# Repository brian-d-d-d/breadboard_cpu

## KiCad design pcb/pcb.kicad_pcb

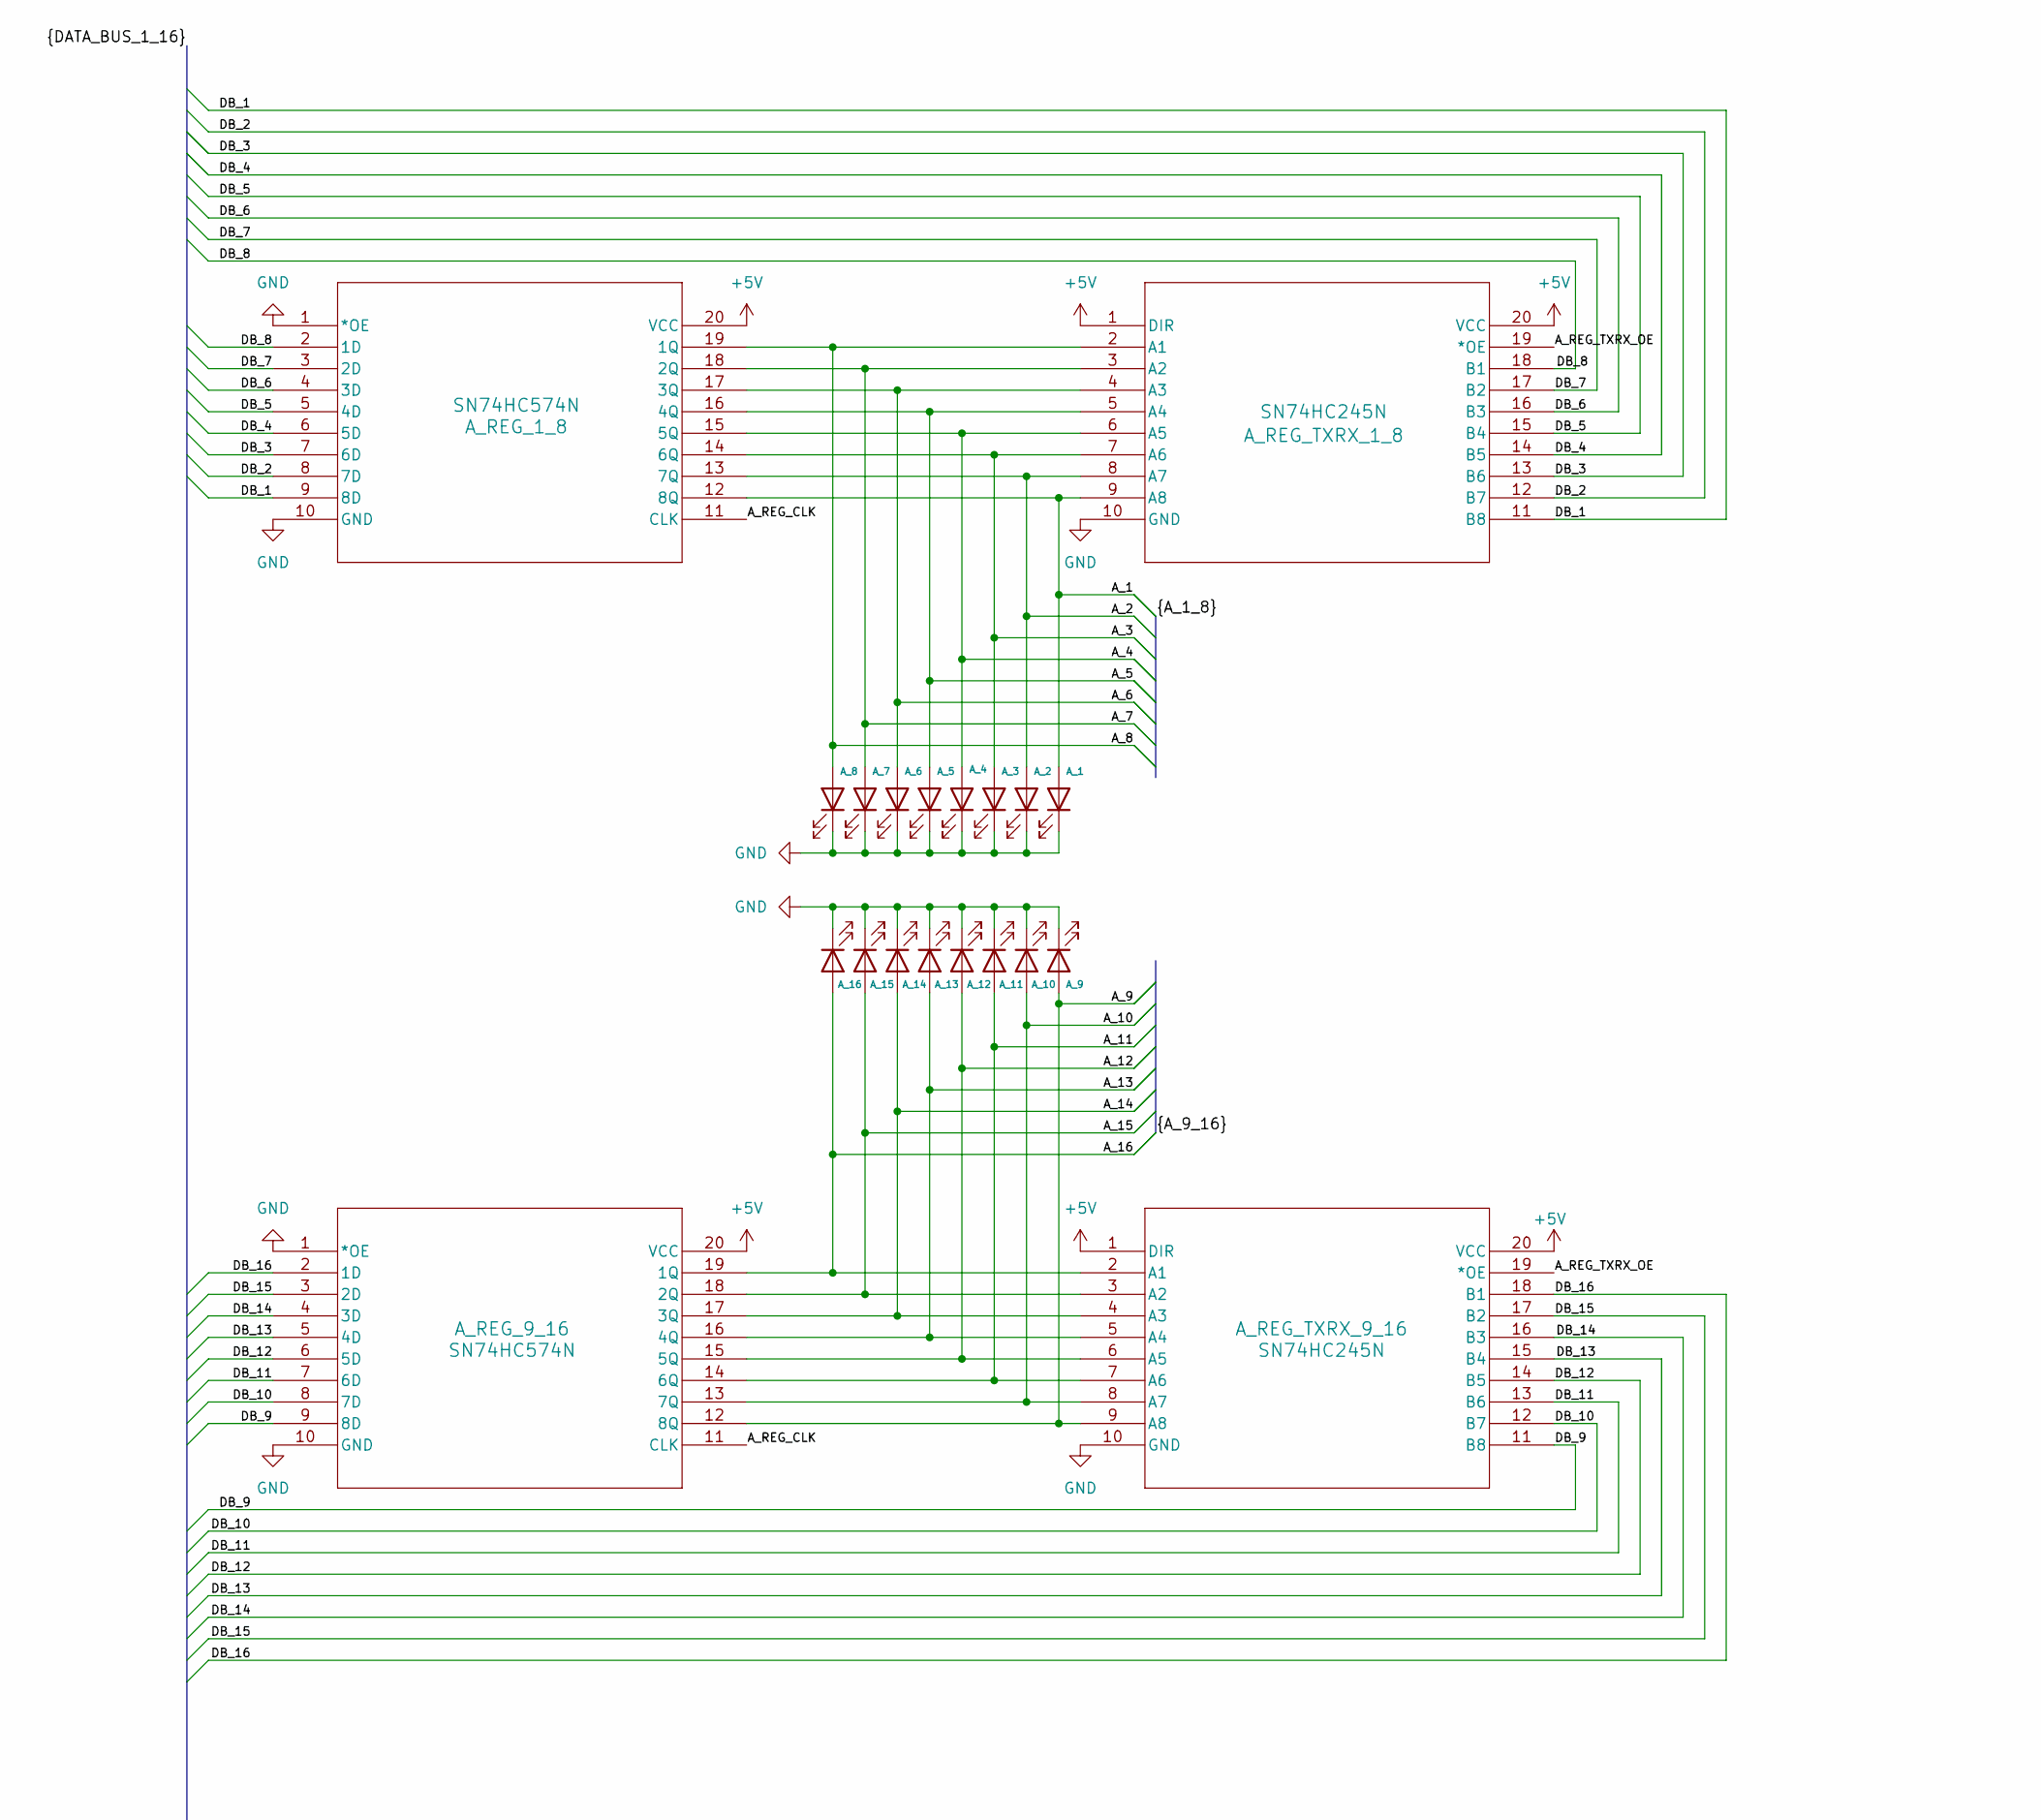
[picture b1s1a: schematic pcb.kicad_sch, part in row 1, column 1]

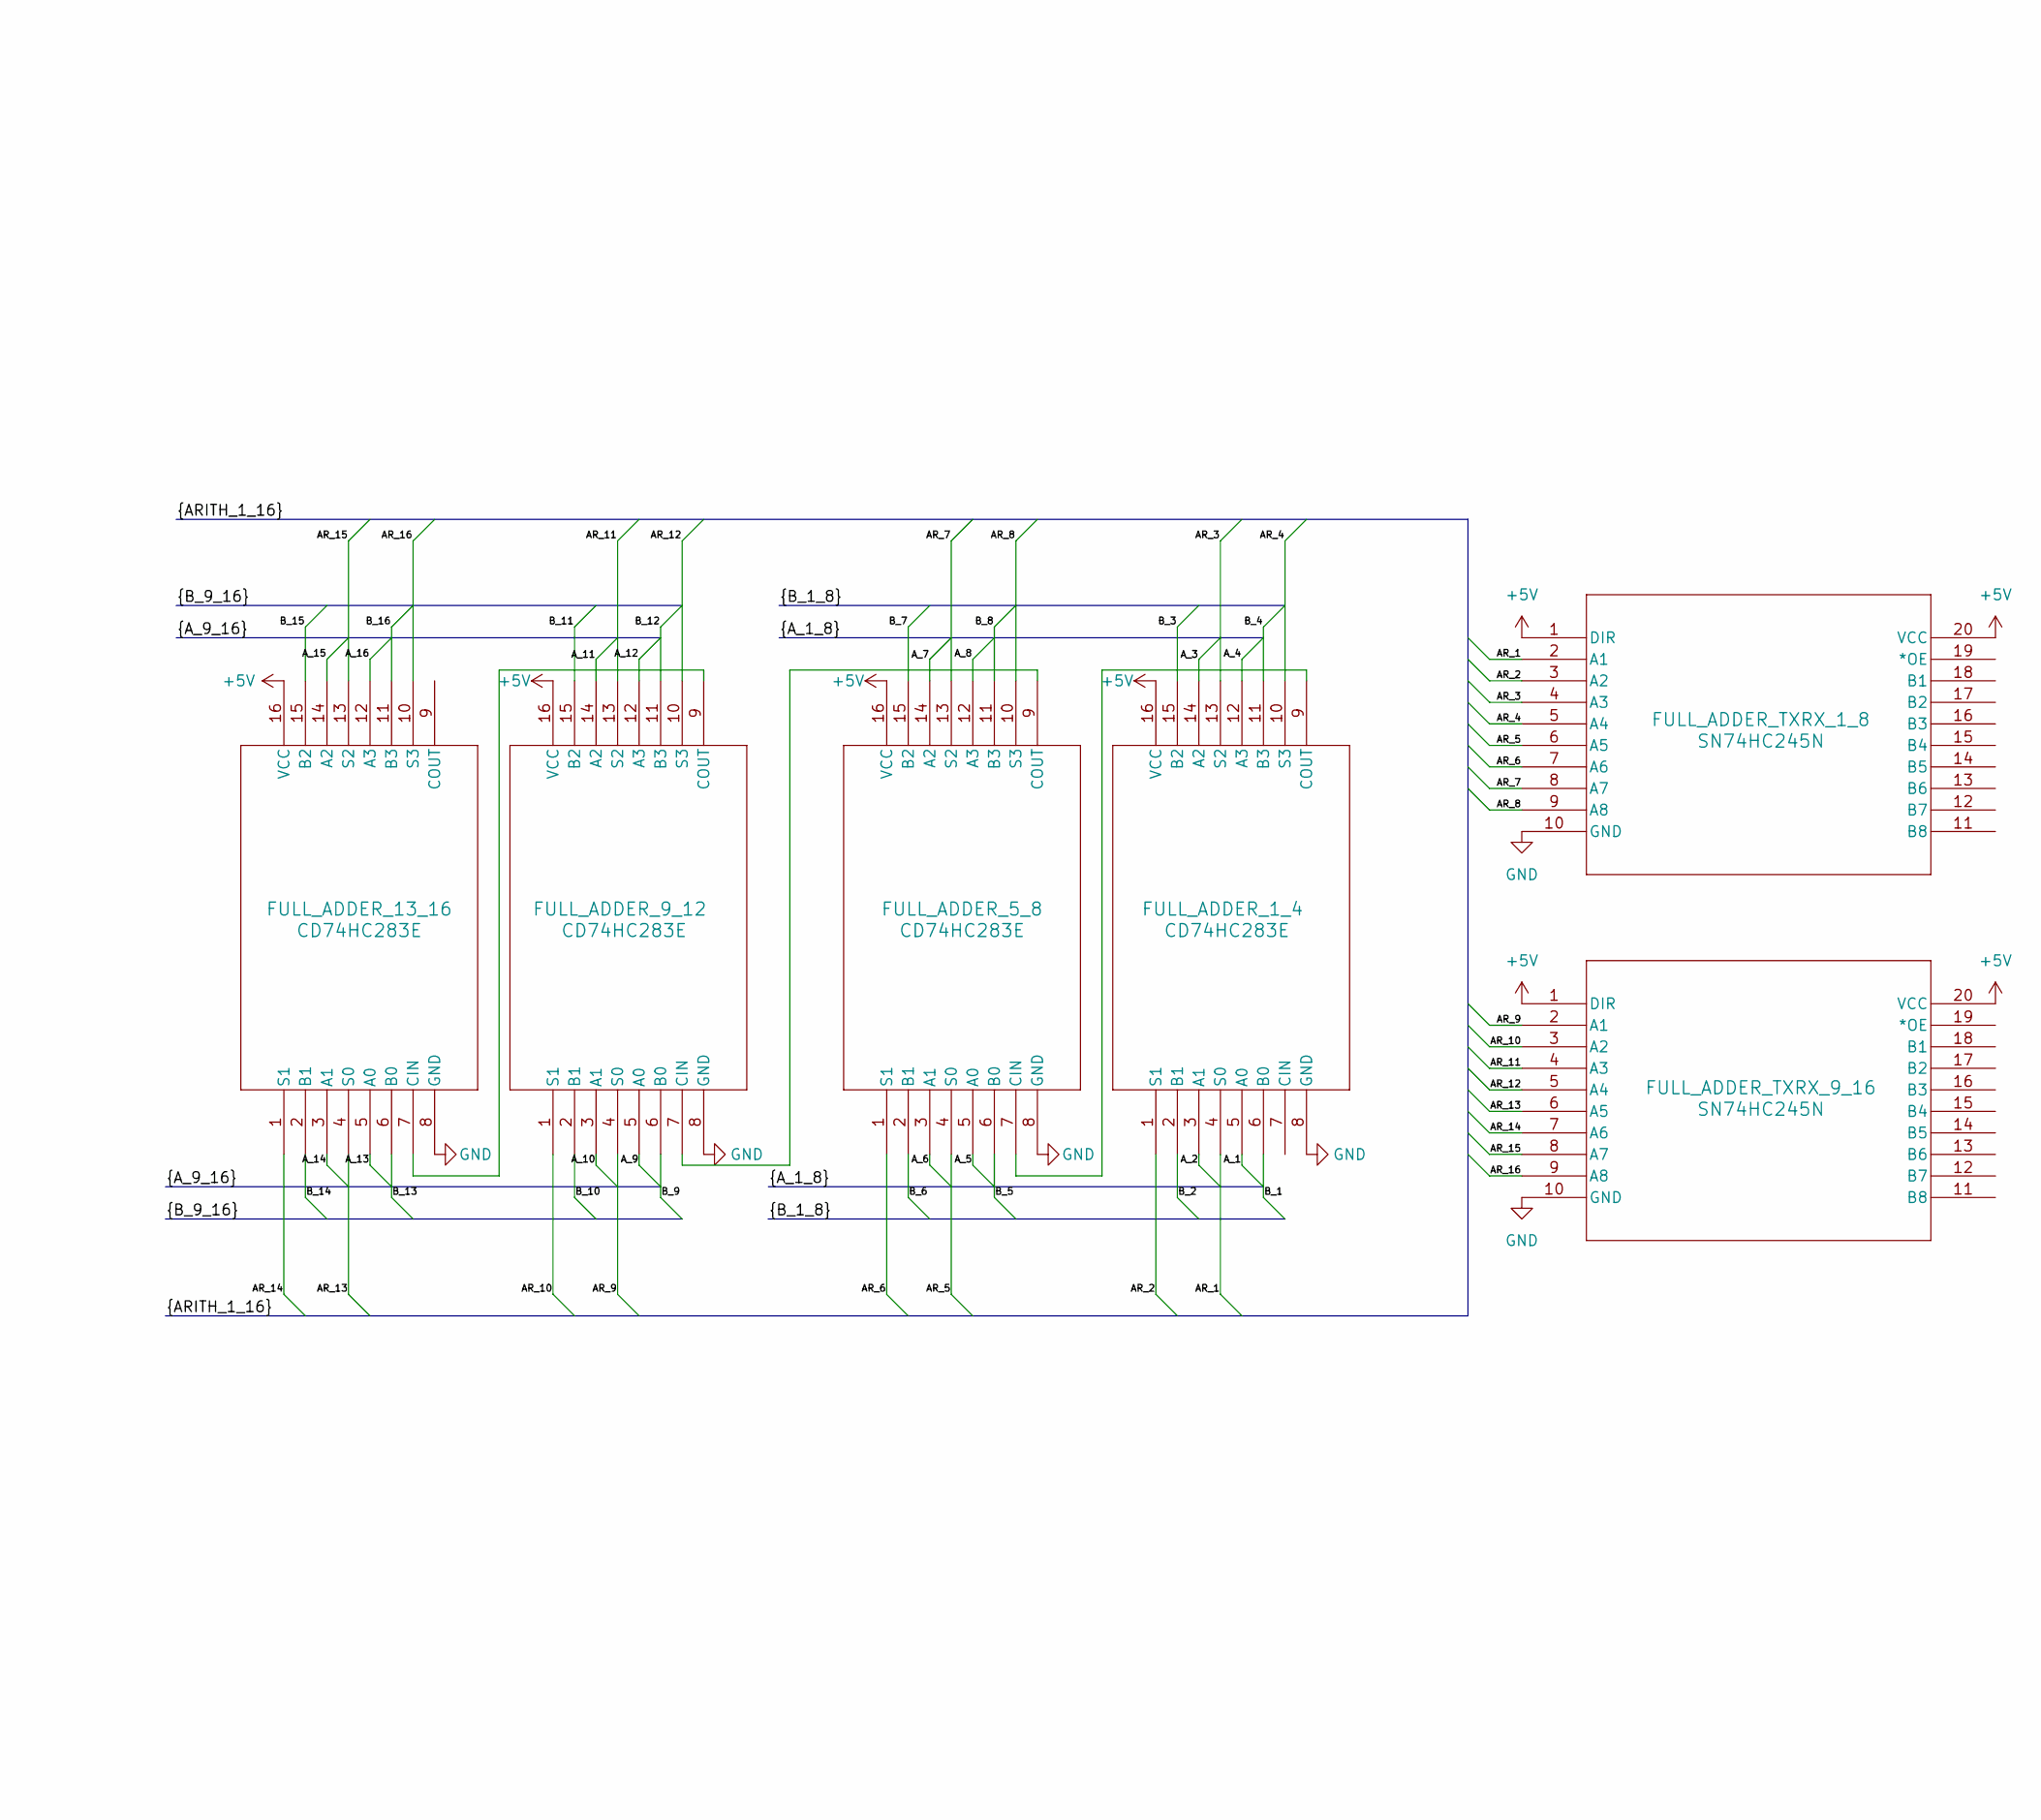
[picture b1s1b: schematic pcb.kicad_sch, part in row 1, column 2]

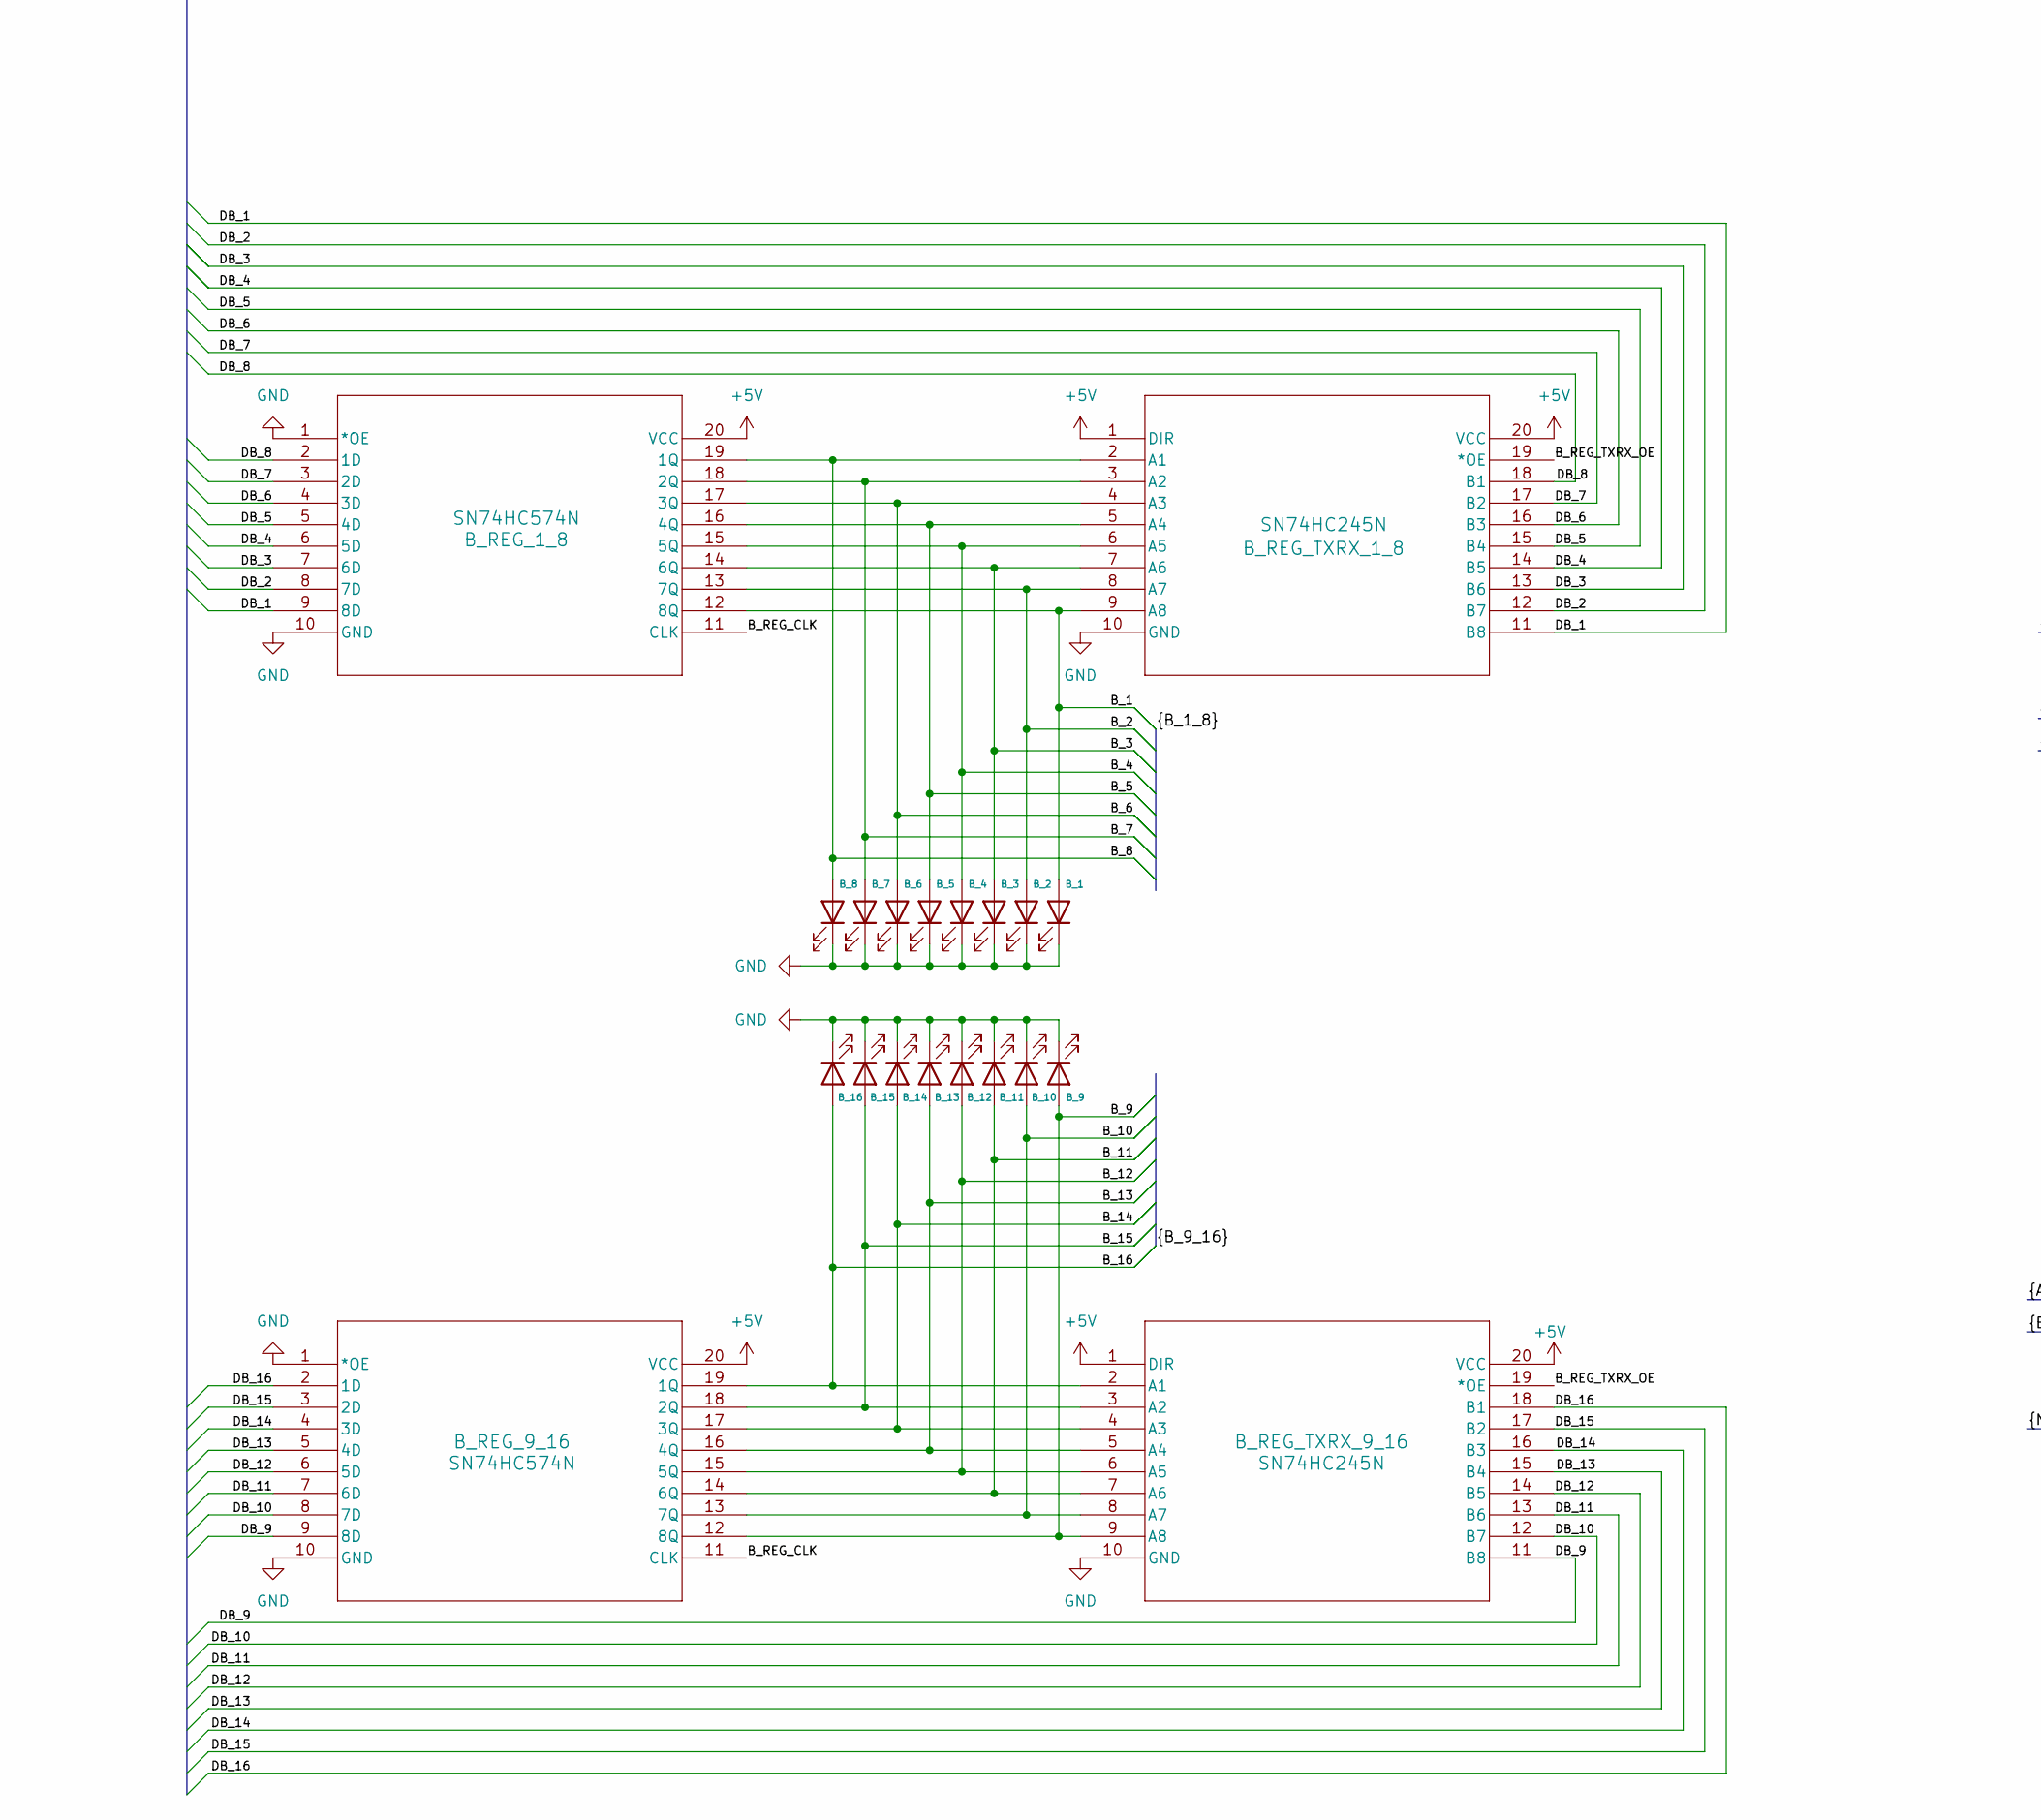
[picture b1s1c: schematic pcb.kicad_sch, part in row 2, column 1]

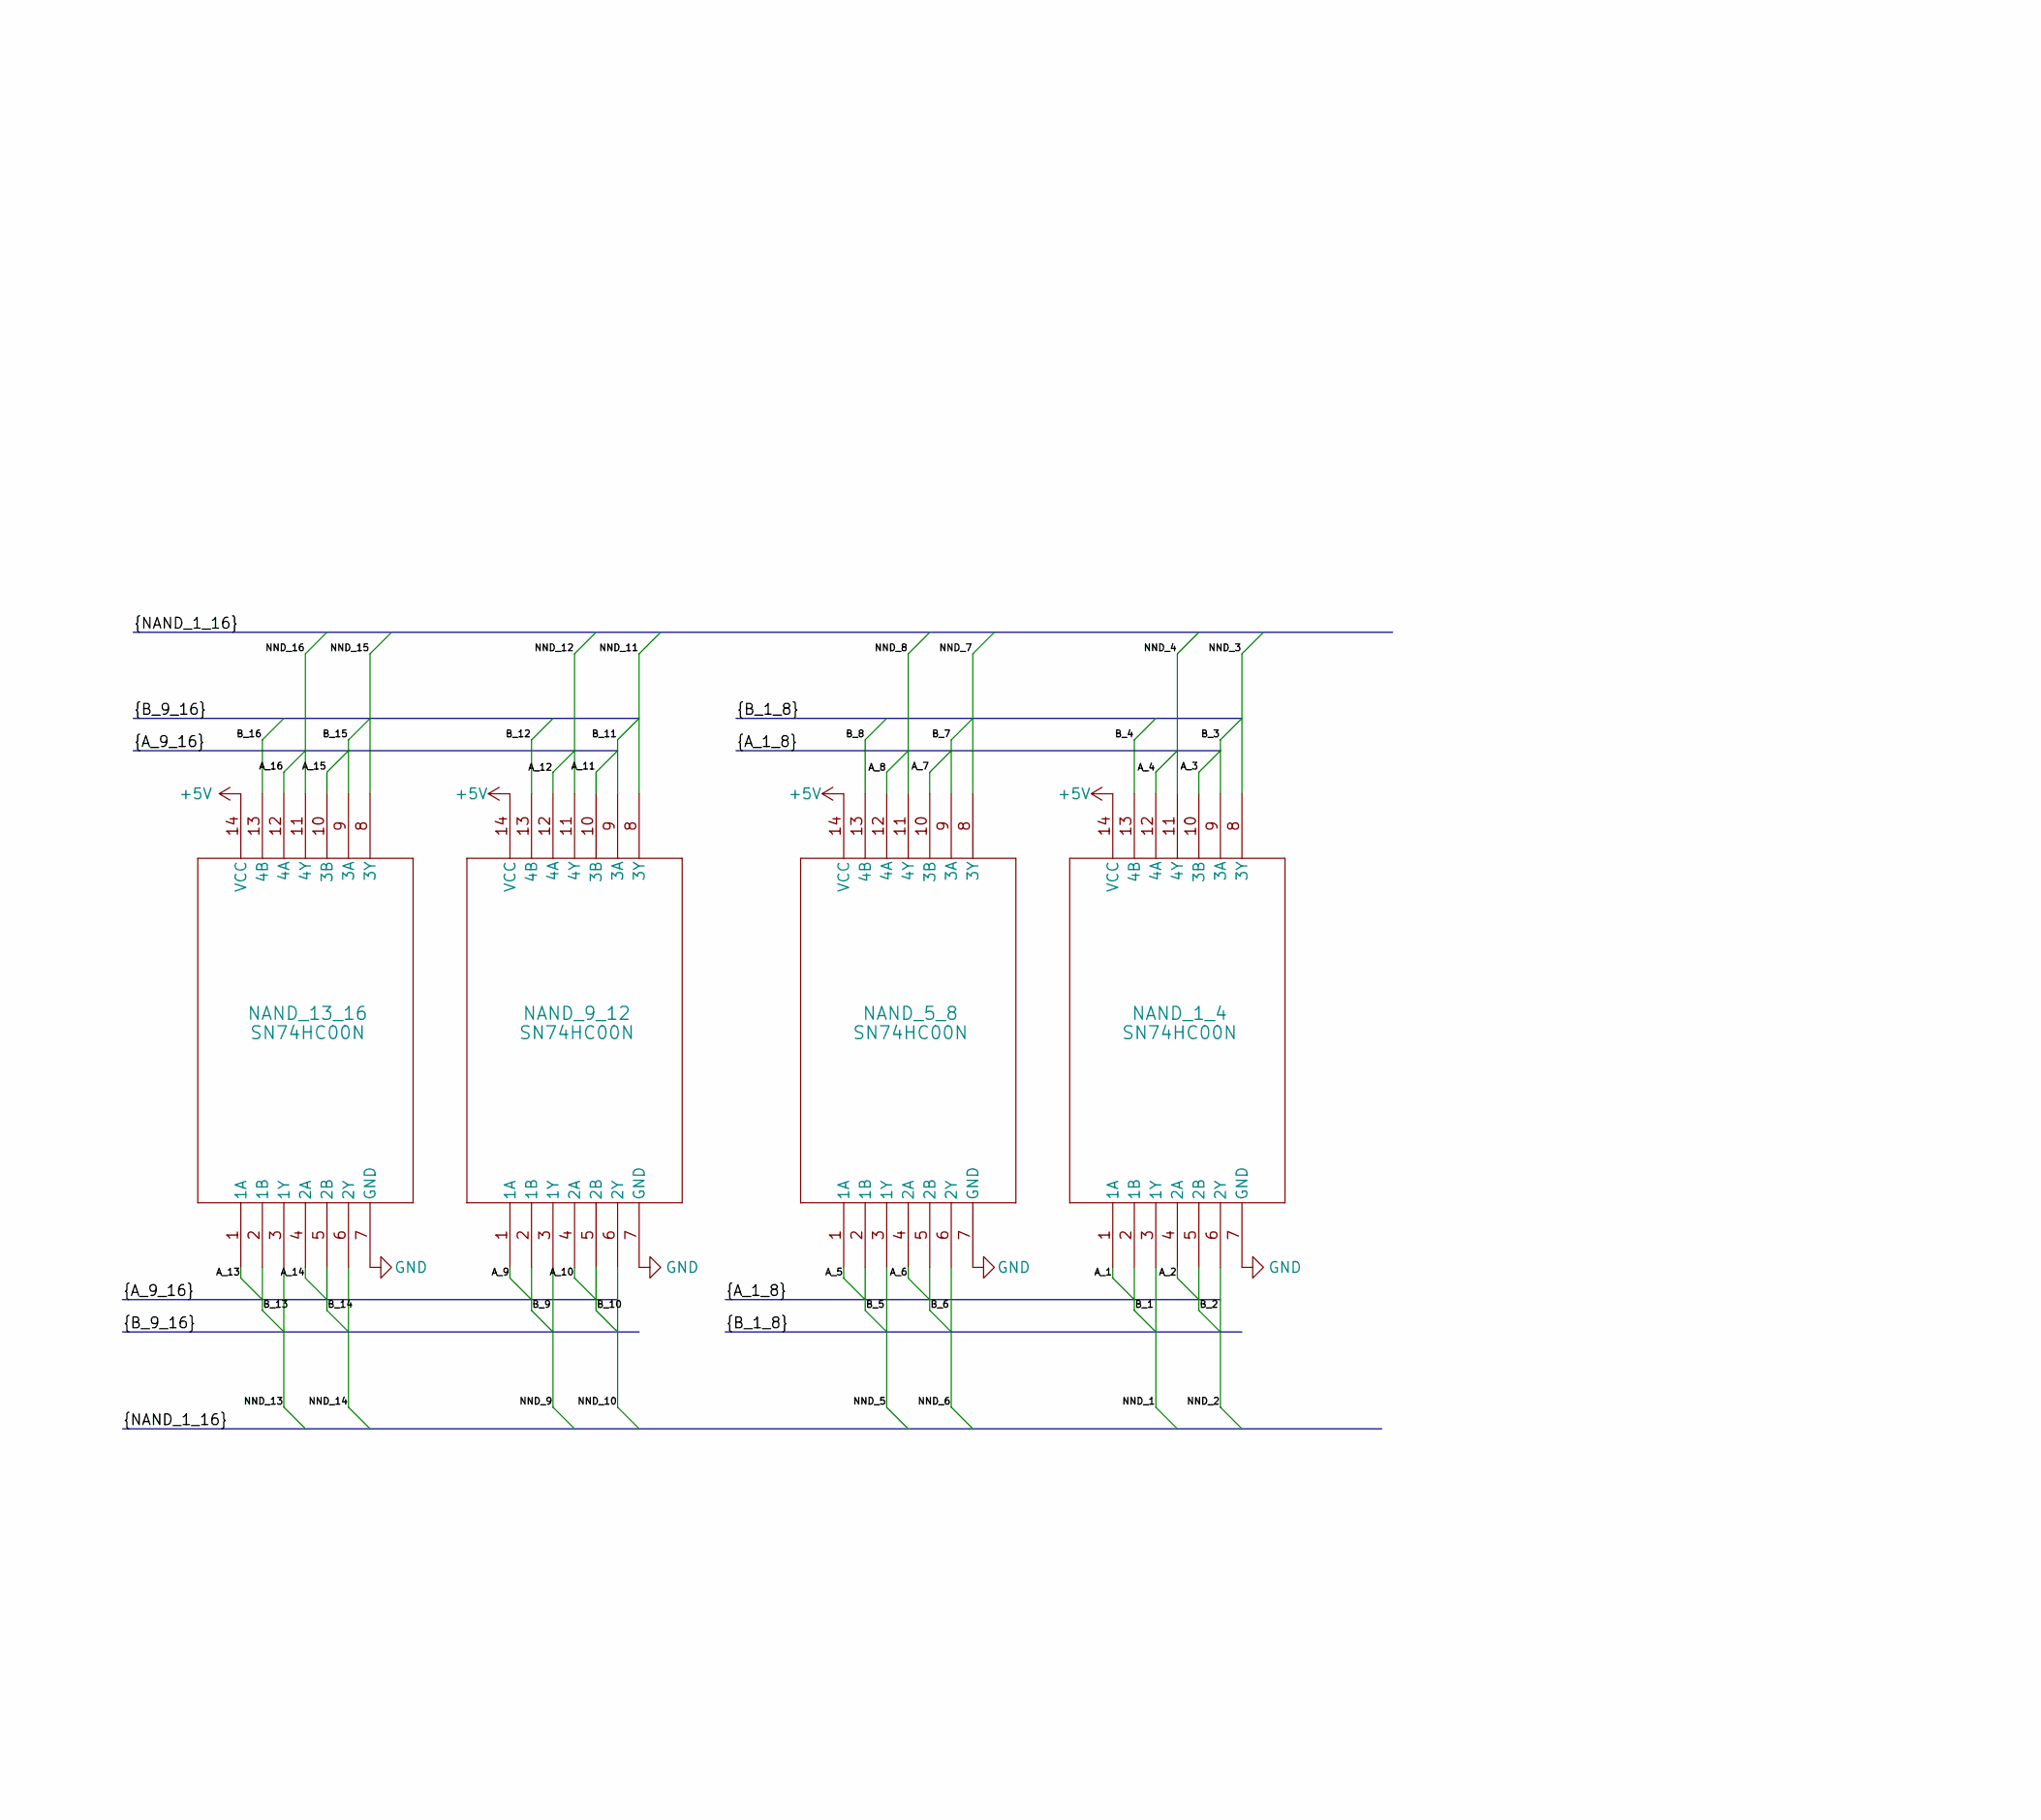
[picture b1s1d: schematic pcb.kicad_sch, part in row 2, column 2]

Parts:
A_1, A_2, A_3, A_4, A_5, A_6, A_7, A_8, A_9, A_10, A_11, A_12, A_13, A_14, A_15, A_16: LED; LED_D5.0mm
A_REG_1_8, A_REG_9_16: SN74HC574N; 20pdip
A_REG_TXRX_1_8, A_REG_TXRX_9_16: SN74HC245N; 20pdip
B_1, B_2, B_3, B_4, B_5, B_6, B_7, B_8, B_9, B_10, B_11, B_12, B_13, B_14, B_15, B_16: LED; LED_D5.0mm
B_REG_1_8, B_REG_9_16: SN74HC574N; 20pdip
B_REG_TXRX_1_8, B_REG_TXRX_9_16: SN74HC245N; 20pdip
FULL_ADDER_1_4, FULL_ADDER_5_8, FULL_ADDER_9_12, FULL_ADDER_13_16: CD74HC283E; 16pdip
FULL_ADDER_TXRX_1_8, FULL_ADDER_TXRX_9_16: SN74HC245N; 20pdip
NAND_1_4, NAND_5_8, NAND_9_12, NAND_13_16: SN74HC00N; 14pdip

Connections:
+5V: A_REG_1_8.20 (VCC), A_REG_9_16.20 (VCC), A_REG_TXRX_1_8.1 (DIR), A_REG_TXRX_1_8.20 (VCC), A_REG_TXRX_9_16.1 (DIR), A_REG_TXRX_9_16.20 (VCC), B_REG_1_8.20 (VCC), B_REG_9_16.20 (VCC), B_REG_TXRX_1_8.1 (DIR), B_REG_TXRX_1_8.20 (VCC), B_REG_TXRX_9_16.1 (DIR), B_REG_TXRX_9_16.20 (VCC), FULL_ADDER_1_4.16 (VCC), FULL_ADDER_5_8.16 (VCC), FULL_ADDER_9_12.16 (VCC), FULL_ADDER_13_16.16 (VCC), FULL_ADDER_TXRX_1_8.1 (DIR), FULL_ADDER_TXRX_1_8.20 (VCC), FULL_ADDER_TXRX_9_16.1 (DIR), FULL_ADDER_TXRX_9_16.20 (VCC), NAND_1_4.14 (VCC), NAND_5_8.14 (VCC), NAND_9_12.14 (VCC), NAND_13_16.14 (VCC)
/AR_1: FULL_ADDER_1_4.4 (S0), FULL_ADDER_TXRX_1_8.2 (A1)
/AR_2: FULL_ADDER_1_4.1 (S1), FULL_ADDER_TXRX_1_8.3 (A2)
/AR_3: FULL_ADDER_1_4.13 (S2), FULL_ADDER_TXRX_1_8.4 (A3)
/AR_4: FULL_ADDER_1_4.10 (S3), FULL_ADDER_TXRX_1_8.5 (A4)
/AR_5: FULL_ADDER_5_8.4 (S0), FULL_ADDER_TXRX_1_8.6 (A5)
/AR_6: FULL_ADDER_5_8.1 (S1), FULL_ADDER_TXRX_1_8.7 (A6)
/AR_7: FULL_ADDER_5_8.13 (S2), FULL_ADDER_TXRX_1_8.8 (A7)
/AR_8: FULL_ADDER_5_8.10 (S3), FULL_ADDER_TXRX_1_8.9 (A8)
/AR_9: FULL_ADDER_9_12.4 (S0), FULL_ADDER_TXRX_9_16.2 (A1)
/AR_10: FULL_ADDER_9_12.1 (S1), FULL_ADDER_TXRX_9_16.3 (A2)
/AR_11: FULL_ADDER_9_12.13 (S2), FULL_ADDER_TXRX_9_16.4 (A3)
/AR_12: FULL_ADDER_9_12.10 (S3), FULL_ADDER_TXRX_9_16.5 (A4)
/AR_13: FULL_ADDER_13_16.4 (S0), FULL_ADDER_TXRX_9_16.6 (A5)
/AR_14: FULL_ADDER_13_16.1 (S1), FULL_ADDER_TXRX_9_16.7 (A6)
/AR_15: FULL_ADDER_13_16.13 (S2), FULL_ADDER_TXRX_9_16.8 (A7)
/AR_16: FULL_ADDER_13_16.10 (S3), FULL_ADDER_TXRX_9_16.9 (A8)
/A_1: A_1.2 (A), A_REG_1_8.12 (8Q), A_REG_TXRX_1_8.9 (A8), FULL_ADDER_1_4.5 (A0), NAND_1_4.1 (1A)
/A_2: A_2.2 (A), A_REG_1_8.13 (7Q), A_REG_TXRX_1_8.8 (A7), FULL_ADDER_1_4.3 (A1), NAND_1_4.4 (2A)
/A_3: A_3.2 (A), A_REG_1_8.14 (6Q), A_REG_TXRX_1_8.7 (A6), FULL_ADDER_1_4.14 (A2), NAND_1_4.10 (3B)
/A_4: A_4.2 (A), A_REG_1_8.15 (5Q), A_REG_TXRX_1_8.6 (A5), FULL_ADDER_1_4.12 (A3), NAND_1_4.12 (4A)
/A_5: A_5.2 (A), A_REG_1_8.16 (4Q), A_REG_TXRX_1_8.5 (A4), FULL_ADDER_5_8.5 (A0), NAND_5_8.1 (1A)
/A_6: A_6.2 (A), A_REG_1_8.17 (3Q), A_REG_TXRX_1_8.4 (A3), FULL_ADDER_5_8.3 (A1), NAND_5_8.4 (2A)
/A_7: A_7.2 (A), A_REG_1_8.18 (2Q), A_REG_TXRX_1_8.3 (A2), FULL_ADDER_5_8.14 (A2), NAND_5_8.10 (3B)
/A_8: A_8.2 (A), A_REG_1_8.19 (1Q), A_REG_TXRX_1_8.2 (A1), FULL_ADDER_5_8.12 (A3), NAND_5_8.12 (4A)
/A_9: A_9.2 (A), A_REG_9_16.12 (8Q), A_REG_TXRX_9_16.9 (A8), FULL_ADDER_9_12.5 (A0), NAND_9_12.1 (1A)
/A_10: A_10.2 (A), A_REG_9_16.13 (7Q), A_REG_TXRX_9_16.8 (A7), FULL_ADDER_9_12.3 (A1), NAND_9_12.4 (2A)
/A_11: A_11.2 (A), A_REG_9_16.14 (6Q), A_REG_TXRX_9_16.7 (A6), FULL_ADDER_9_12.14 (A2), NAND_9_12.10 (3B)
/A_12: A_12.2 (A), A_REG_9_16.15 (5Q), A_REG_TXRX_9_16.6 (A5), FULL_ADDER_9_12.12 (A3), NAND_9_12.12 (4A)
/A_13: A_13.2 (A), A_REG_9_16.16 (4Q), A_REG_TXRX_9_16.5 (A4), FULL_ADDER_13_16.5 (A0), NAND_13_16.1 (1A)
/A_14: A_14.2 (A), A_REG_9_16.17 (3Q), A_REG_TXRX_9_16.4 (A3), FULL_ADDER_13_16.3 (A1), NAND_13_16.4 (2A)
/A_15: A_15.2 (A), A_REG_9_16.18 (2Q), A_REG_TXRX_9_16.3 (A2), FULL_ADDER_13_16.14 (A2), NAND_13_16.10 (3B)
/A_16: A_16.2 (A), A_REG_9_16.19 (1Q), A_REG_TXRX_9_16.2 (A1), FULL_ADDER_13_16.12 (A3), NAND_13_16.12 (4A)
/A_REG_CLK: A_REG_1_8.11 (CLK), A_REG_9_16.11 (CLK)
/A_REG_TXRX_OE: A_REG_TXRX_1_8.19 (*OE), A_REG_TXRX_9_16.19 (*OE)
/B_1: B_1.2 (A), B_REG_1_8.12 (8Q), B_REG_TXRX_1_8.9 (A8), FULL_ADDER_1_4.6 (B0), NAND_1_4.2 (1B)
/B_2: B_2.2 (A), B_REG_1_8.13 (7Q), B_REG_TXRX_1_8.8 (A7), FULL_ADDER_1_4.2 (B1), NAND_1_4.5 (2B)
/B_3: B_3.2 (A), B_REG_1_8.14 (6Q), B_REG_TXRX_1_8.7 (A6), FULL_ADDER_1_4.15 (B2), NAND_1_4.9 (3A)
/B_4: B_4.2 (A), B_REG_1_8.15 (5Q), B_REG_TXRX_1_8.6 (A5), FULL_ADDER_1_4.11 (B3), NAND_1_4.13 (4B)
/B_5: B_5.2 (A), B_REG_1_8.16 (4Q), B_REG_TXRX_1_8.5 (A4), FULL_ADDER_5_8.6 (B0), NAND_5_8.2 (1B)
/B_6: B_6.2 (A), B_REG_1_8.17 (3Q), B_REG_TXRX_1_8.4 (A3), FULL_ADDER_5_8.2 (B1), NAND_5_8.5 (2B)
/B_7: B_7.2 (A), B_REG_1_8.18 (2Q), B_REG_TXRX_1_8.3 (A2), FULL_ADDER_5_8.15 (B2), NAND_5_8.9 (3A)
/B_8: B_8.2 (A), B_REG_1_8.19 (1Q), B_REG_TXRX_1_8.2 (A1), FULL_ADDER_5_8.11 (B3), NAND_5_8.13 (4B)
/B_9: B_9.2 (A), B_REG_9_16.12 (8Q), B_REG_TXRX_9_16.9 (A8), FULL_ADDER_9_12.6 (B0), NAND_9_12.2 (1B)
/B_10: B_10.2 (A), B_REG_9_16.13 (7Q), B_REG_TXRX_9_16.8 (A7), FULL_ADDER_9_12.2 (B1), NAND_9_12.5 (2B)
/B_11: B_11.2 (A), B_REG_9_16.14 (6Q), B_REG_TXRX_9_16.7 (A6), FULL_ADDER_9_12.15 (B2), NAND_9_12.9 (3A)
/B_12: B_12.2 (A), B_REG_9_16.15 (5Q), B_REG_TXRX_9_16.6 (A5), FULL_ADDER_9_12.11 (B3), NAND_9_12.13 (4B)
/B_13: B_13.2 (A), B_REG_9_16.16 (4Q), B_REG_TXRX_9_16.5 (A4), FULL_ADDER_13_16.6 (B0), NAND_13_16.2 (1B)
/B_14: B_14.2 (A), B_REG_9_16.17 (3Q), B_REG_TXRX_9_16.4 (A3), FULL_ADDER_13_16.2 (B1), NAND_13_16.5 (2B)
/B_15: B_15.2 (A), B_REG_9_16.18 (2Q), B_REG_TXRX_9_16.3 (A2), FULL_ADDER_13_16.15 (B2), NAND_13_16.9 (3A)
/B_16: B_16.2 (A), B_REG_9_16.19 (1Q), B_REG_TXRX_9_16.2 (A1), FULL_ADDER_13_16.11 (B3), NAND_13_16.13 (4B)
/B_REG_CLK: B_REG_1_8.11 (CLK), B_REG_9_16.11 (CLK)
/B_REG_TXRX_OE: B_REG_TXRX_1_8.19 (*OE), B_REG_TXRX_9_16.19 (*OE)
/DB_1: A_REG_1_8.9 (8D), A_REG_TXRX_1_8.11 (B8), B_REG_1_8.9 (8D), B_REG_TXRX_1_8.11 (B8)
/DB_2: A_REG_1_8.8 (7D), A_REG_TXRX_1_8.12 (B7), B_REG_1_8.8 (7D), B_REG_TXRX_1_8.12 (B7)
/DB_3: A_REG_1_8.7 (6D), A_REG_TXRX_1_8.13 (B6), B_REG_1_8.7 (6D), B_REG_TXRX_1_8.13 (B6)
/DB_4: A_REG_1_8.6 (5D), A_REG_TXRX_1_8.14 (B5), B_REG_1_8.6 (5D), B_REG_TXRX_1_8.14 (B5)
/DB_5: A_REG_1_8.5 (4D), A_REG_TXRX_1_8.15 (B4), B_REG_1_8.5 (4D), B_REG_TXRX_1_8.15 (B4)
/DB_6: A_REG_1_8.4 (3D), A_REG_TXRX_1_8.16 (B3), B_REG_1_8.4 (3D), B_REG_TXRX_1_8.16 (B3)
/DB_7: A_REG_1_8.3 (2D), A_REG_TXRX_1_8.17 (B2), B_REG_1_8.3 (2D), B_REG_TXRX_1_8.17 (B2)
/DB_8: A_REG_1_8.2 (1D), A_REG_TXRX_1_8.18 (B1), B_REG_1_8.2 (1D), B_REG_TXRX_1_8.18 (B1)
/DB_9: A_REG_9_16.9 (8D), A_REG_TXRX_9_16.11 (B8), B_REG_9_16.9 (8D), B_REG_TXRX_9_16.11 (B8)
/DB_10: A_REG_9_16.8 (7D), A_REG_TXRX_9_16.12 (B7), B_REG_9_16.8 (7D), B_REG_TXRX_9_16.12 (B7)
/DB_11: A_REG_9_16.7 (6D), A_REG_TXRX_9_16.13 (B6), B_REG_9_16.7 (6D), B_REG_TXRX_9_16.13 (B6)
/DB_12: A_REG_9_16.6 (5D), A_REG_TXRX_9_16.14 (B5), B_REG_9_16.6 (5D), B_REG_TXRX_9_16.14 (B5)
/DB_13: A_REG_9_16.5 (4D), A_REG_TXRX_9_16.15 (B4), B_REG_9_16.5 (4D), B_REG_TXRX_9_16.15 (B4)
/DB_14: A_REG_9_16.4 (3D), A_REG_TXRX_9_16.16 (B3), B_REG_9_16.4 (3D), B_REG_TXRX_9_16.16 (B3)
/DB_15: A_REG_9_16.3 (2D), A_REG_TXRX_9_16.17 (B2), B_REG_9_16.3 (2D), B_REG_TXRX_9_16.17 (B2)
/DB_16: A_REG_9_16.2 (1D), A_REG_TXRX_9_16.18 (B1), B_REG_9_16.2 (1D), B_REG_TXRX_9_16.18 (B1)
/NND_1: NAND_1_4.3 (1Y)
/NND_2: NAND_1_4.6 (2Y)
/NND_3: NAND_1_4.8 (3Y)
/NND_4: NAND_1_4.11 (4Y)
/NND_5: NAND_5_8.3 (1Y)
/NND_6: NAND_5_8.6 (2Y)
/NND_7: NAND_5_8.8 (3Y)
/NND_8: NAND_5_8.11 (4Y)
/NND_9: NAND_9_12.3 (1Y)
/NND_10: NAND_9_12.6 (2Y)
/NND_11: NAND_9_12.8 (3Y)
/NND_12: NAND_9_12.11 (4Y)
/NND_13: NAND_13_16.3 (1Y)
/NND_14: NAND_13_16.6 (2Y)
/NND_15: NAND_13_16.8 (3Y)
/NND_16: NAND_13_16.11 (4Y)
GND: A_1.1 (K), A_2.1 (K), A_3.1 (K), A_4.1 (K), A_5.1 (K), A_6.1 (K), A_7.1 (K), A_8.1 (K), A_9.1 (K), A_10.1 (K), A_11.1 (K), A_12.1 (K), A_13.1 (K), A_14.1 (K), A_15.1 (K), A_16.1 (K), A_REG_1_8.1 (*OE), A_REG_1_8.10 (GND), A_REG_9_16.1 (*OE), A_REG_9_16.10 (GND), A_REG_TXRX_1_8.10 (GND), A_REG_TXRX_9_16.10 (GND), B_1.1 (K), B_2.1 (K), B_3.1 (K), B_4.1 (K), B_5.1 (K), B_6.1 (K), B_7.1 (K), B_8.1 (K), B_9.1 (K), B_10.1 (K), B_11.1 (K), B_12.1 (K), B_13.1 (K), B_14.1 (K), B_15.1 (K), B_16.1 (K), B_REG_1_8.1 (*OE), B_REG_1_8.10 (GND), B_REG_9_16.1 (*OE), B_REG_9_16.10 (GND), B_REG_TXRX_1_8.10 (GND), B_REG_TXRX_9_16.10 (GND), FULL_ADDER_1_4.8 (GND), FULL_ADDER_5_8.8 (GND), FULL_ADDER_9_12.8 (GND), FULL_ADDER_13_16.8 (GND), FULL_ADDER_TXRX_1_8.10 (GND), FULL_ADDER_TXRX_9_16.10 (GND), NAND_1_4.7 (GND), NAND_5_8.7 (GND), NAND_9_12.7 (GND), NAND_13_16.7 (GND)
unnamed: FULL_ADDER_1_4.9 (COUT), FULL_ADDER_5_8.7 (CIN)
unnamed: FULL_ADDER_5_8.9 (COUT), FULL_ADDER_9_12.7 (CIN)
unnamed: FULL_ADDER_9_12.9 (COUT), FULL_ADDER_13_16.7 (CIN)

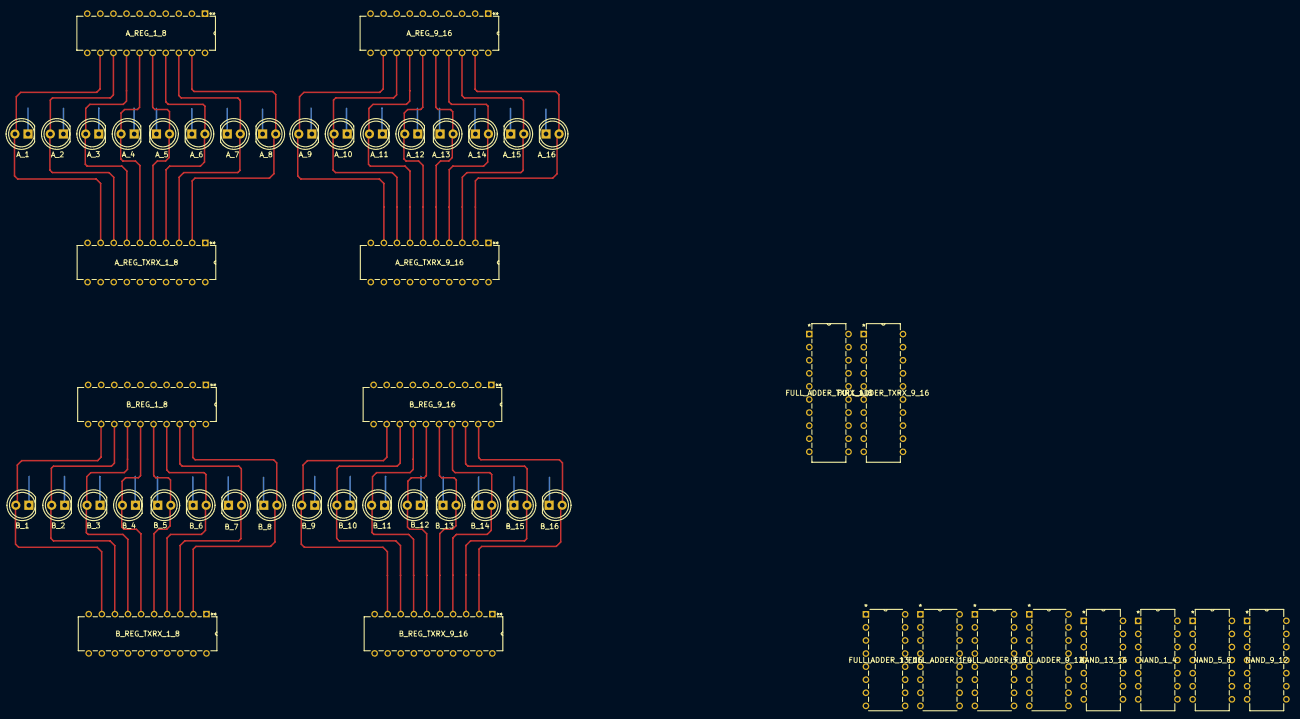
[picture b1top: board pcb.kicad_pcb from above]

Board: 2 copper layers, 50 parts (0 on the bottom side), 73 nets.

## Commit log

2026-05-06 feat: wrote functions for getting and setting bits for pins
2026-05-07 refactor: renamed pins function
2026-05-07 feat: functions written for handling getting and setting commands senet over serial
2026-05-07 refactor: renamed command_string to command
2026-05-07 refactor: remove undeeded len paramater in command handling functions
2026-05-07 feat: using commands to set bus values now works
2026-05-08 refactor: changed receiving to use readBytesUntil
2026-05-08 feat: change mode command added
2026-05-08 feat: created test files and setup a function to run lists of commands
2026-05-08 chore: moved CLOCK_SPEED to defines.py file
2026-05-08 chore: added CLOCK_SPEED to defines.py file forgot about it in last commit
2026-05-08 chore: removed uneeded readme files
2026-05-08 chore: added 4th bus
2026-05-08 feat: test written for checking read and writing to ram
2026-05-18 feat: test written for testing 8 bit register
2026-05-18 refactor: changed tests so the same serial port instance is used for all tests in the same file
2026-05-21 feat: wrote test for alu
2026-05-25 feat: new bus added and full tests written for alu
2026-05-25 feat: fixed tests for checking the simple arithmetic and logic functionality
2026-05-25 feat: test written for a 4 byte unsigned add
2026-05-26 refactor: rearranged repo to add folder for pcb files
2026-05-26 feat: added pcb files
2026-05-26 feat: low bits of register a and b pcb design done
2026-05-27 feat: pcb routed for 16 bit a register
2026-05-27 feat: schematic for full adder mostly done
